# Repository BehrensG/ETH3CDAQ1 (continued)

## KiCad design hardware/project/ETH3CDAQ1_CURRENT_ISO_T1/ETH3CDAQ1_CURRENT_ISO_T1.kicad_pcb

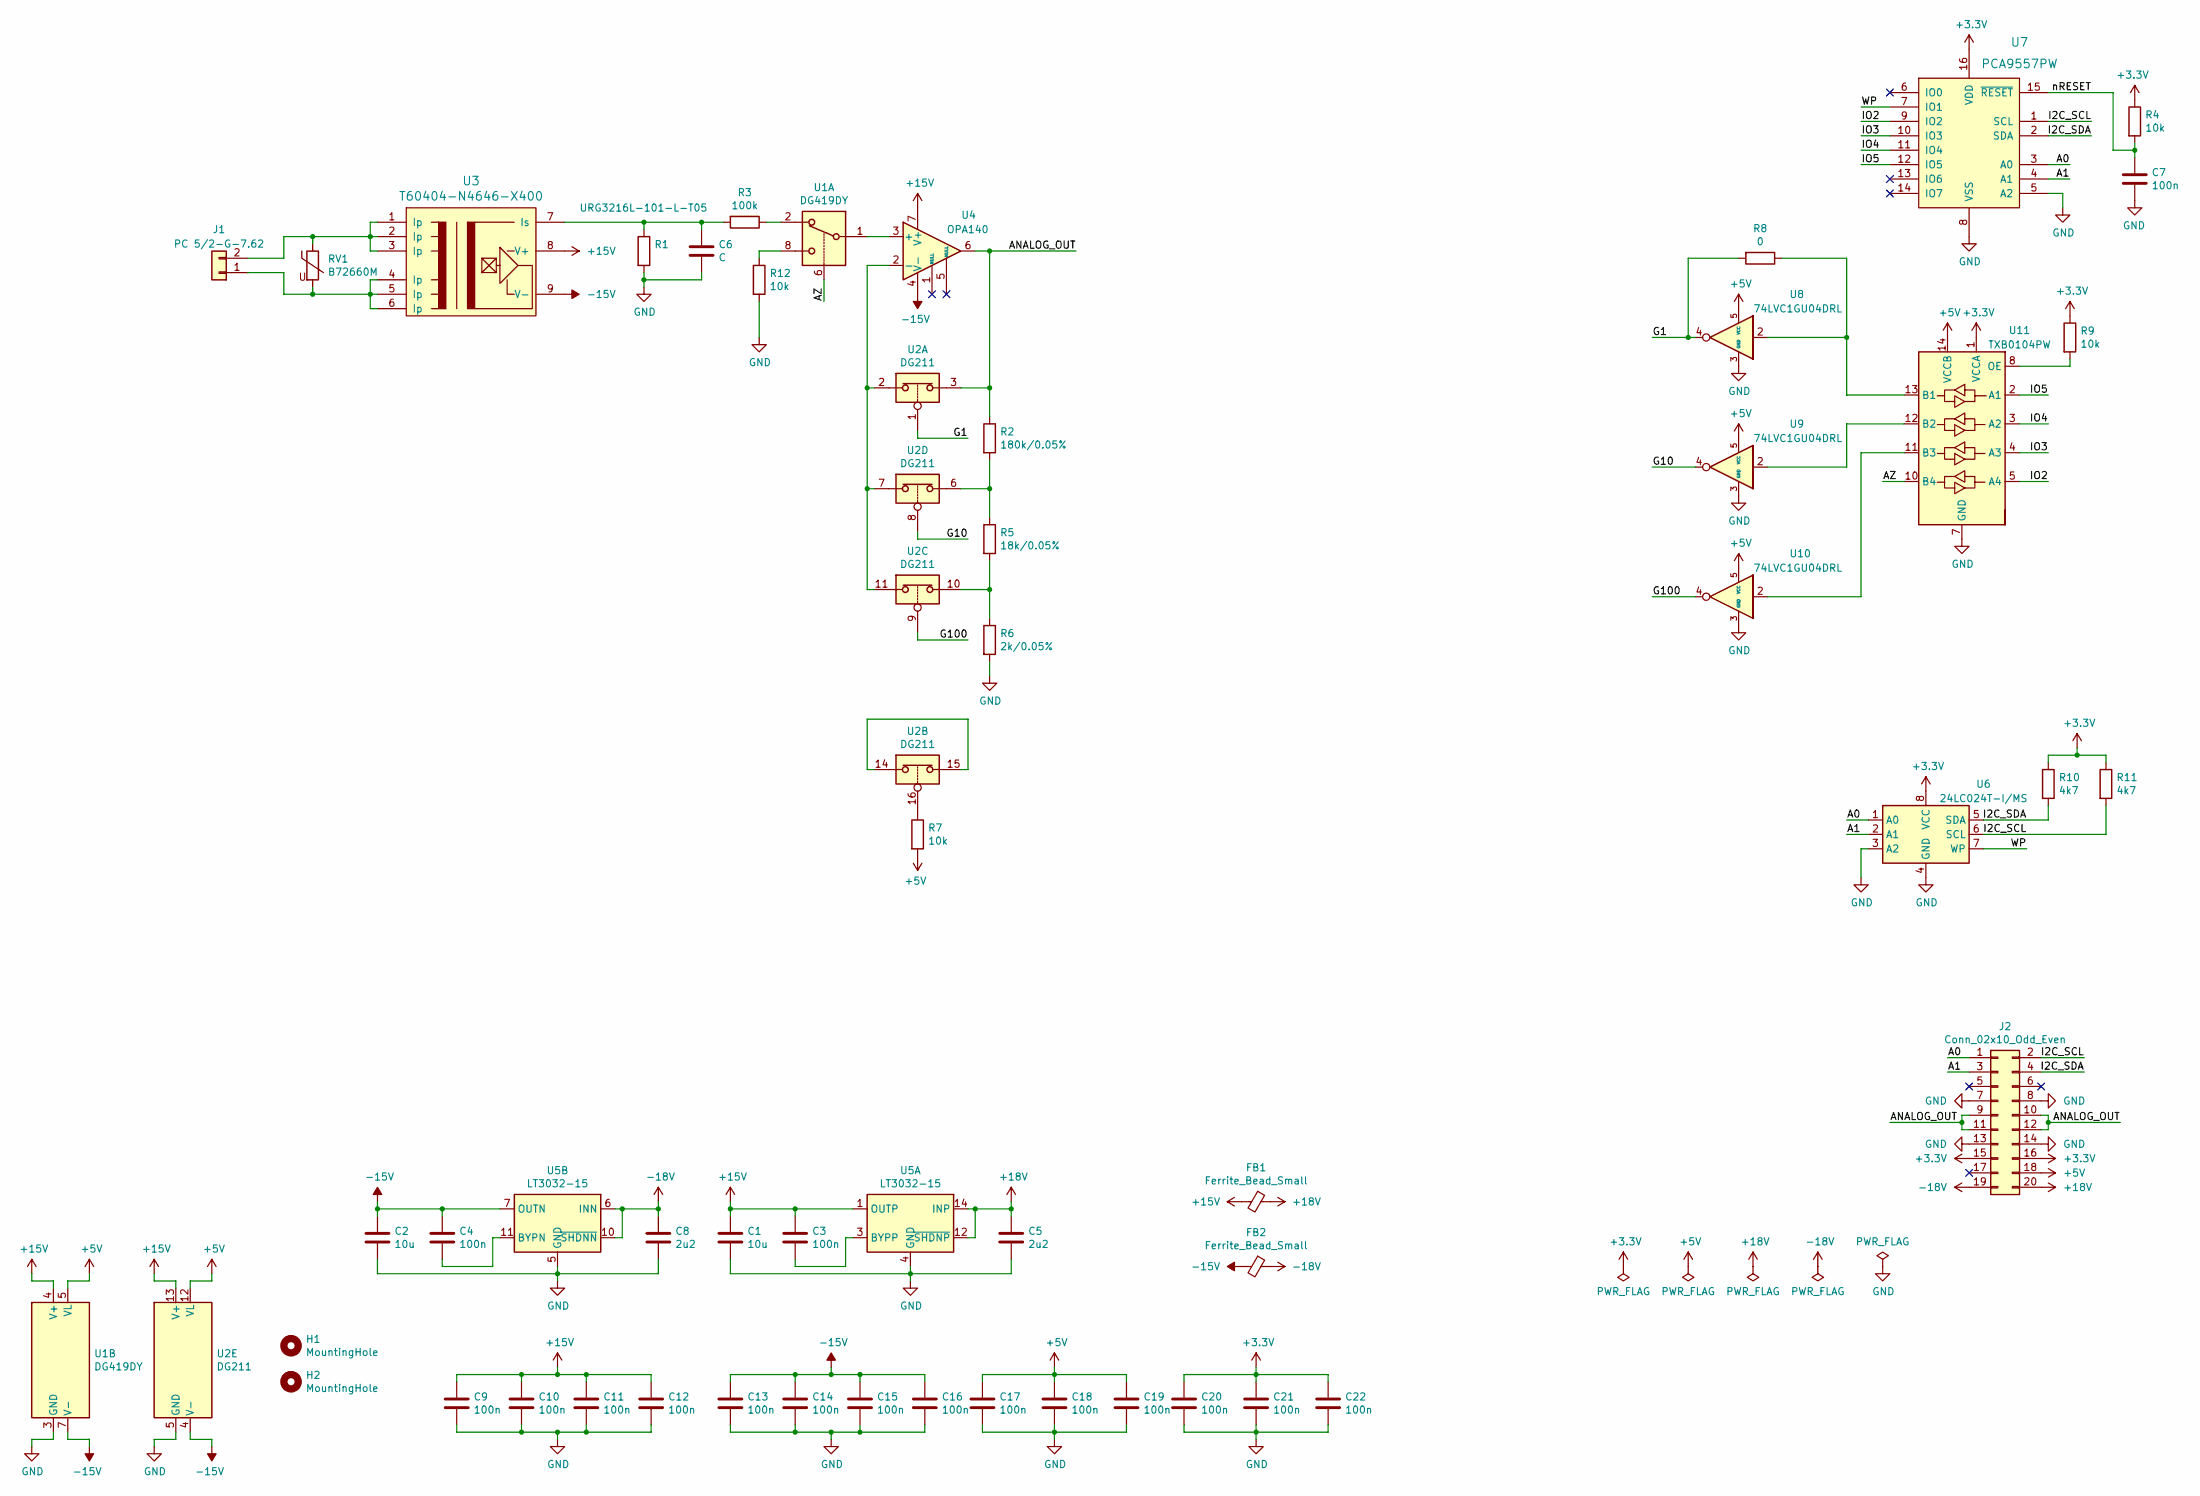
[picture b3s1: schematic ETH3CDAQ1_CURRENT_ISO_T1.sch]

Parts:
C1, C2: 10u; C_0603_1608Metric_Pad1.08x0.95mm_HandSolder
C3, C4, C7, C9, C10, C11, C12, C13, C14, C15, C16, C17, C18, C19, C20, C21, C22: 100n; C_0603_1608Metric_Pad1.08x0.95mm_HandSolder
C5, C8: 2u2; C_0603_1608Metric_Pad1.08x0.95mm_HandSolder
C6: C; C_1206_3216Metric_Pad1.33x1.80mm_HandSolder
FB1, FB2: Ferrite_Bead_Small; R_0603_1608Metric_Pad0.98x0.95mm_HandSolder
H1, H2: MountingHole; MountingHole_2.7mm_M2.5_DIN965_Pad
J1: PC 5/2-G-7.62; PC5_2-G-7_62
J2: Conn_02x10_Odd_Even; PinSocket_2x10_P2.54mm_Vertical
R1: URG3216L-101-L-T05; R_1206_3216Metric_Pad1.30x1.75mm_HandSolder
R2: 180k/0.05%; R_0603_1608Metric_Pad0.98x0.95mm_HandSolder
R3: 100k; R_0603_1608Metric_Pad0.98x0.95mm_HandSolder
R4, R7, R9, R12: 10k; R_0603_1608Metric_Pad0.98x0.95mm_HandSolder
R5: 18k/0.05%; R_0603_1608Metric_Pad0.98x0.95mm_HandSolder
R6: 2k/0.05%; R_0603_1608Metric_Pad0.98x0.95mm_HandSolder
R8: 0; R_0603_1608Metric_Pad0.98x0.95mm_HandSolder
R10, R11: 4k7; R_0603_1608Metric_Pad0.98x0.95mm_HandSolder
RV1: B72660M; 4032
U1: DG419DY; SOIC-8_3.9x4.9mm_P1.27mm
U2: DG211; TSSOP-16_4.4x5mm_P0.65mm
U3: T60404-N4646-X400
U4: OPA140; SOIC-8_3.9x4.9mm_P1.27mm
U5: LT3032-15; Linear_DE14MA
U6: 24LC024T-I/MS; MSOP-8_3x3mm_P0.65mm
U7: PCA9557PW; TSSOP-16_4.4x5mm_P0.65mm
U8, U9, U10: 74LVC1GU04DRL; SOT-553
U11: TXB0104PW; TSSOP-14_4.4x5mm_P0.65mm

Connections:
+3V3: C20.1, C21.1, C22.1, J2.15, J2.16, R4.1, R9.1, R10.1, R11.1, U6.8 (VCC), U7.16 (VDD), U11.1 (VCCA)
+5V: C17.1, C18.1, C19.1, J2.18, R7.2, U1.5 (VL), U2.12 (VL), U8.5 (VCC), U9.5 (VCC), U10.5 (VCC), U11.14 (VCCB)
+15V: C1.1, C3.1, C9.1, C10.1, C11.1, C12.1, FB1.2, U1.4 (V+), U2.13 (V+), U3.8 (V+), U4.7 (V+), U5.1 (OUTP)
+18V: C5.1, FB1.1, J2.20, U5.12 (~SHDNP), U5.14 (INP)
-15V: C2.1, C4.1, C13.1, C14.1, C15.1, C16.1, FB2.2, U1.7 (V-), U2.4 (V-), U3.9 (V-), U4.4 (V-), U5.7 (OUTN)
-18V: C8.1, FB2.1, J2.19, U5.6 (INN), U5.9 (INN), U5.10 (~SHDNN)
/A0: J2.1, U6.1 (A0), U7.3 (A0)
/A1: J2.3, U6.2 (A1), U7.4 (A1)
/ANALOG_OUT: J2.9, J2.10, J2.11, J2.12, R2.1, U2.3, U4.6
/AZ: U1.6, U11.10 (B4)
/G1: R8.2, U2.1, U8.4
/G10: U2.8, U9.4
/G100: U2.9, U10.4
/I2C_SCL: J2.2, R11.2, U6.6 (SCL), U7.1 (SCL)
/I2C_SDA: J2.4, R10.2, U6.5 (SDA), U7.2 (SDA)
/IO2: U7.9 (IO2), U11.5 (A4)
/IO3: U7.10 (IO3), U11.4 (A3)
/IO4: U7.11 (IO4), U11.3 (A2)
/IO5: U7.12 (IO5), U11.2 (A1)
/WP: U6.7 (WP), U7.7 (IO1)
/nRESET: C7.1, R4.2, U7.15 (~RESET)
GND: C1.2, C2.2, C5.2, C6.2, C7.2, C8.2, C9.2, C10.2, C11.2, C12.2, C13.2, C14.2, C15.2, C16.2, C17.2, C18.2, C19.2, C20.2, C21.2, C22.2, J2.7, J2.8, J2.13, J2.14, R1.2, R6.2, R12.2, U1.3 (GND), U2.5 (GND), U5.4 (GND), U5.5 (GND), U6.3 (A2), U6.4 (GND), U7.5 (A2), U7.8 (VSS), U8.3 (GND), U9.3 (GND), U10.3 (GND), U11.7 (GND)
unnamed: C3.2, U5.3 (BYPP)
unnamed: C4.2, U5.11 (BYPN)
unnamed: C6.1, R1.1, R3.2, U3.7 (Is)
unnamed: J1.1, RV1.2, U3.4 (Ip), U3.5 (Ip), U3.6 (Ip)
unnamed: J1.2, RV1.1, U3.1 (Ip), U3.2 (Ip), U3.3 (Ip)
unnamed: R2.2, R5.1, U2.6
unnamed: R3.1, U1.2
unnamed: R5.2, R6.1, U2.10
unnamed: R7.1, U2.16
unnamed: R8.1, U8.2, U11.13 (B1)
unnamed: R9.2, U11.8 (OE)
unnamed: R12.1, U1.8
unnamed: U1.1, U4.3 (+)
unnamed: U2.2, U2.7, U2.11, U4.2 (-)
unnamed: U2.14, U2.15
unnamed: U10.2, U11.11 (B3)
unnamed: U9.2, U11.12 (B2)

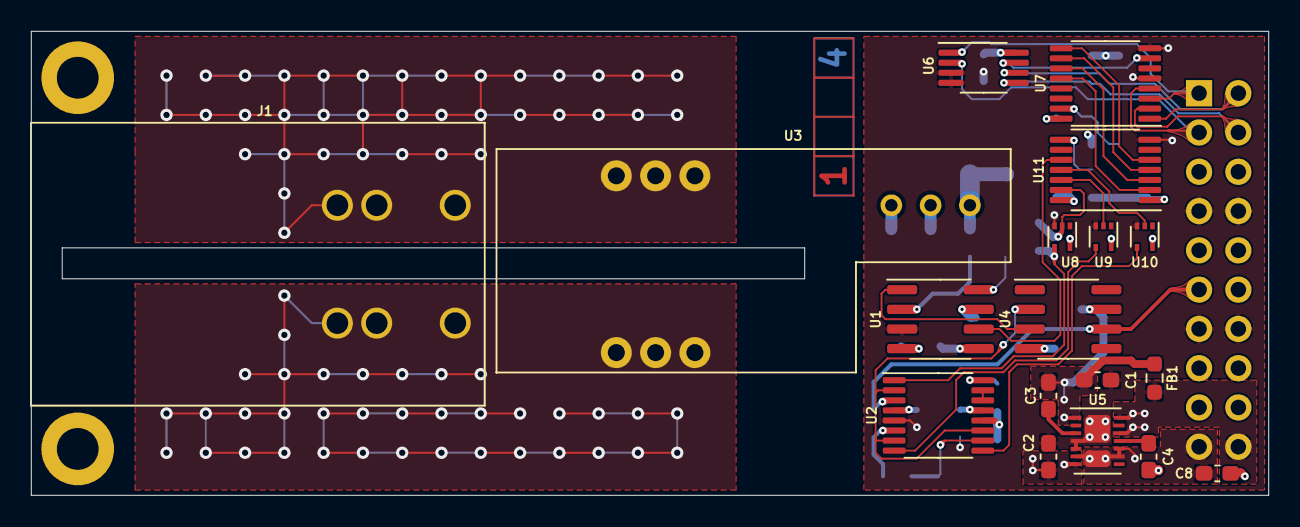
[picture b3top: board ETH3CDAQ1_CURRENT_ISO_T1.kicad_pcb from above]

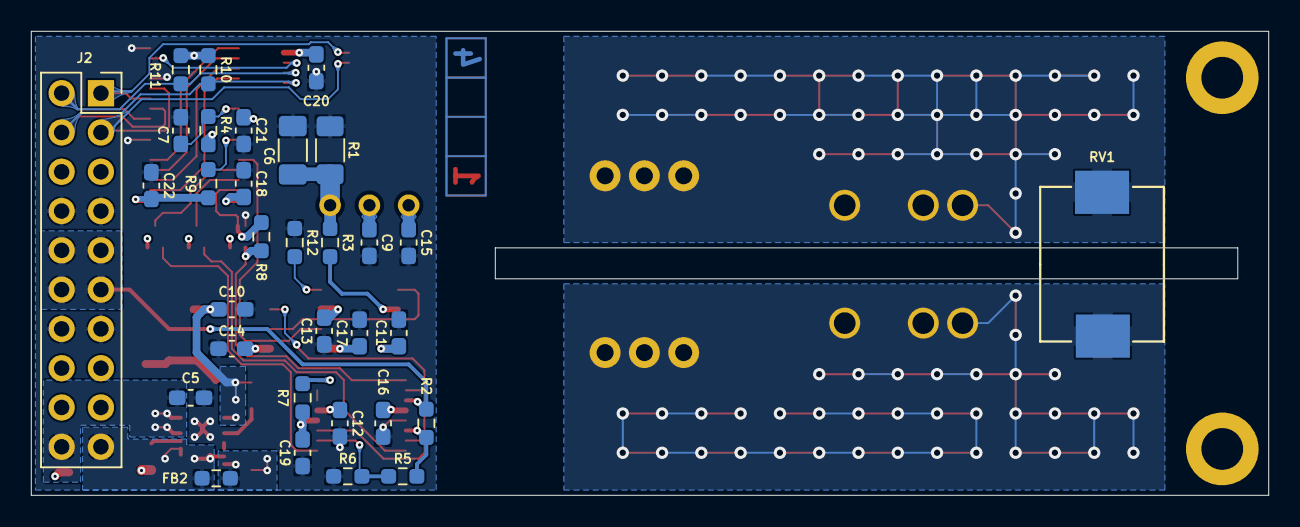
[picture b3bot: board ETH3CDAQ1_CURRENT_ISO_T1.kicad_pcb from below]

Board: 4 copper layers, 80.0 x 30.0 mm, 52 parts (32 on the bottom side), 39 nets.

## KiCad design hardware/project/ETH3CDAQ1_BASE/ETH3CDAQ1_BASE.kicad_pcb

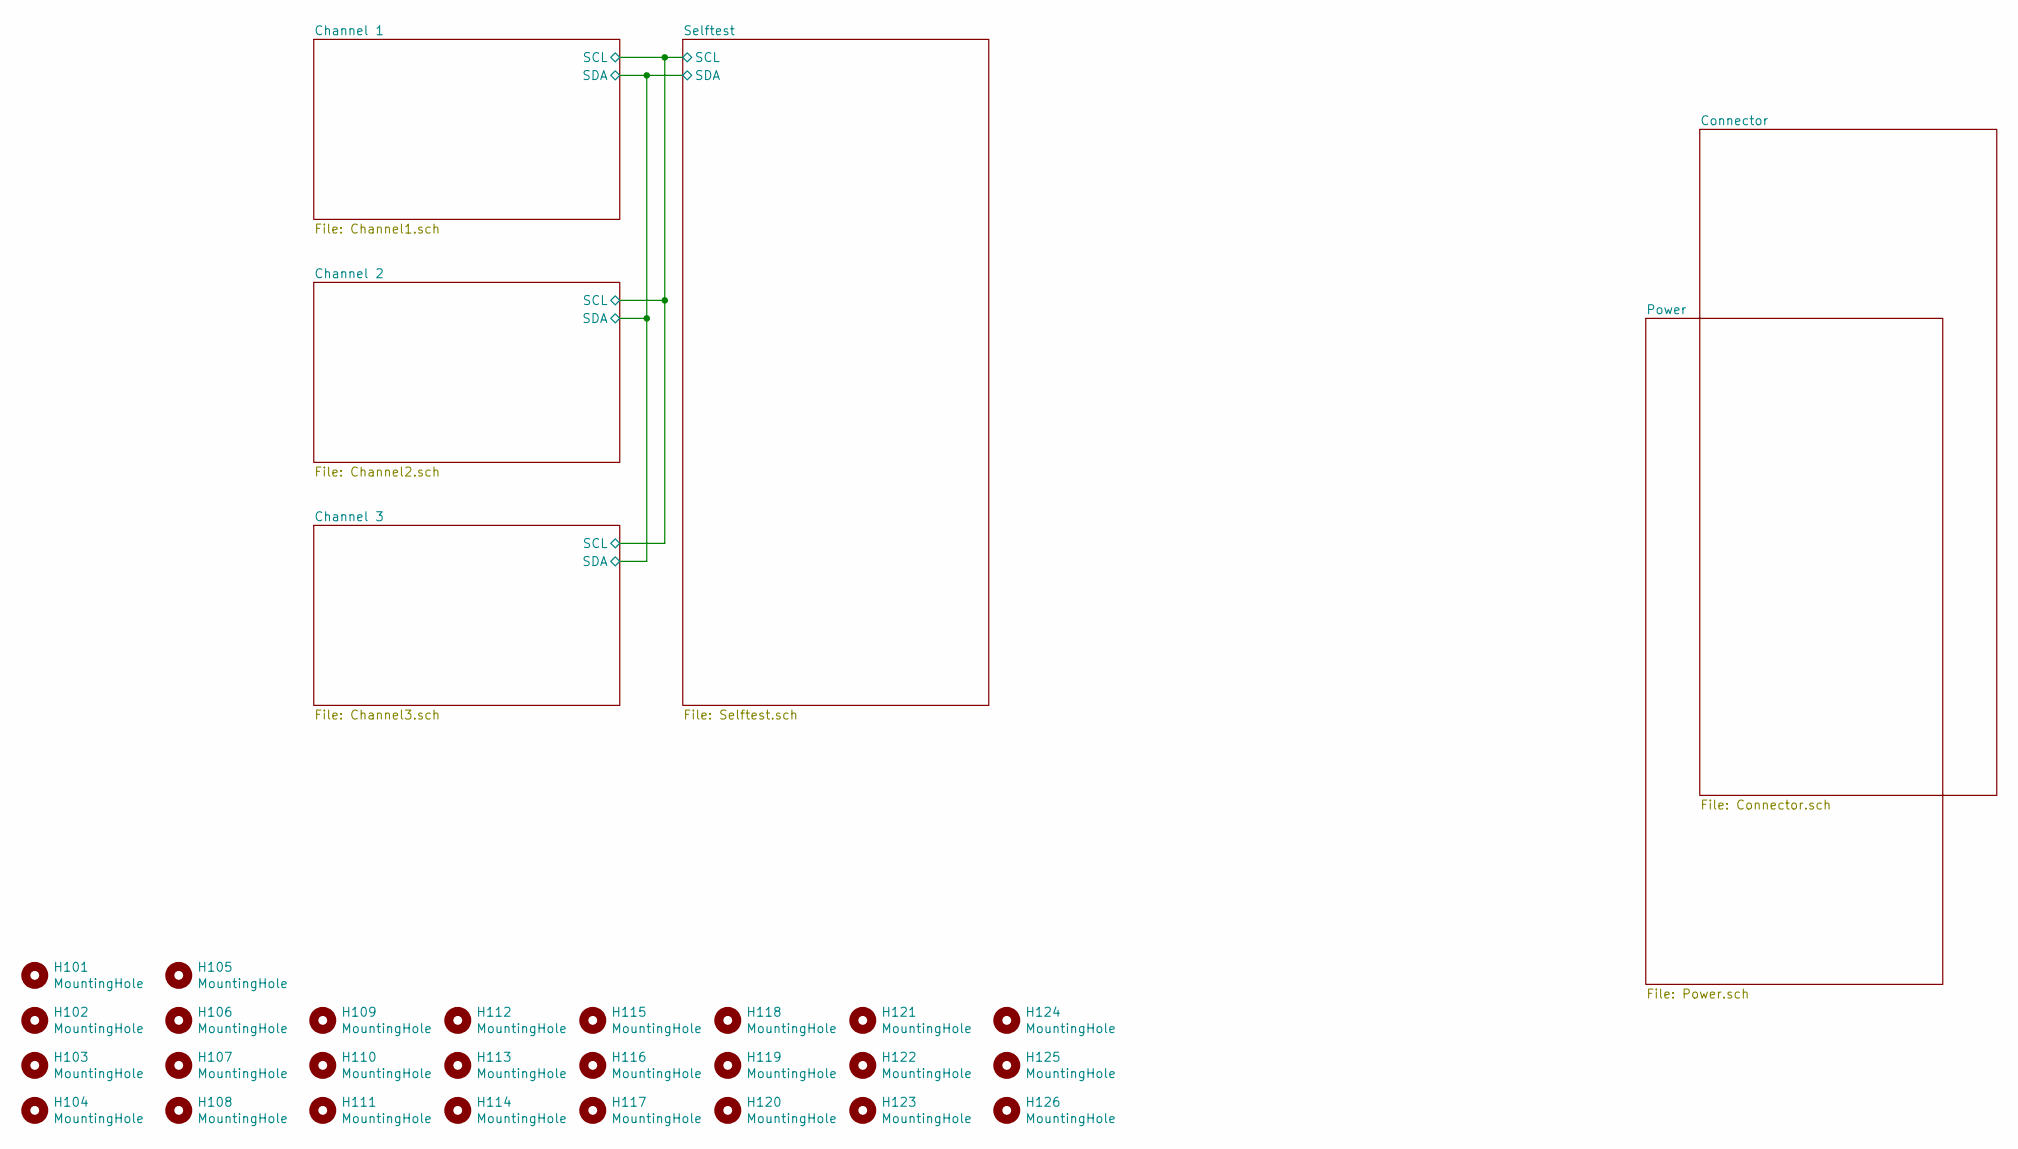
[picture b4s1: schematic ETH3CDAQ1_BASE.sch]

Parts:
H101, H105: MountingHole; MountingHole_3.2mm_M3_DIN965_Pad
H102, H103, H104, H106, H107, H108, H109, H110, H111, H112, H113, H114, H115, H116, H117, H118, H119, H120, H121, H122, H123, H124, H125, H126: MountingHole; MountingHole_2.7mm_M2.5_DIN965_Pad

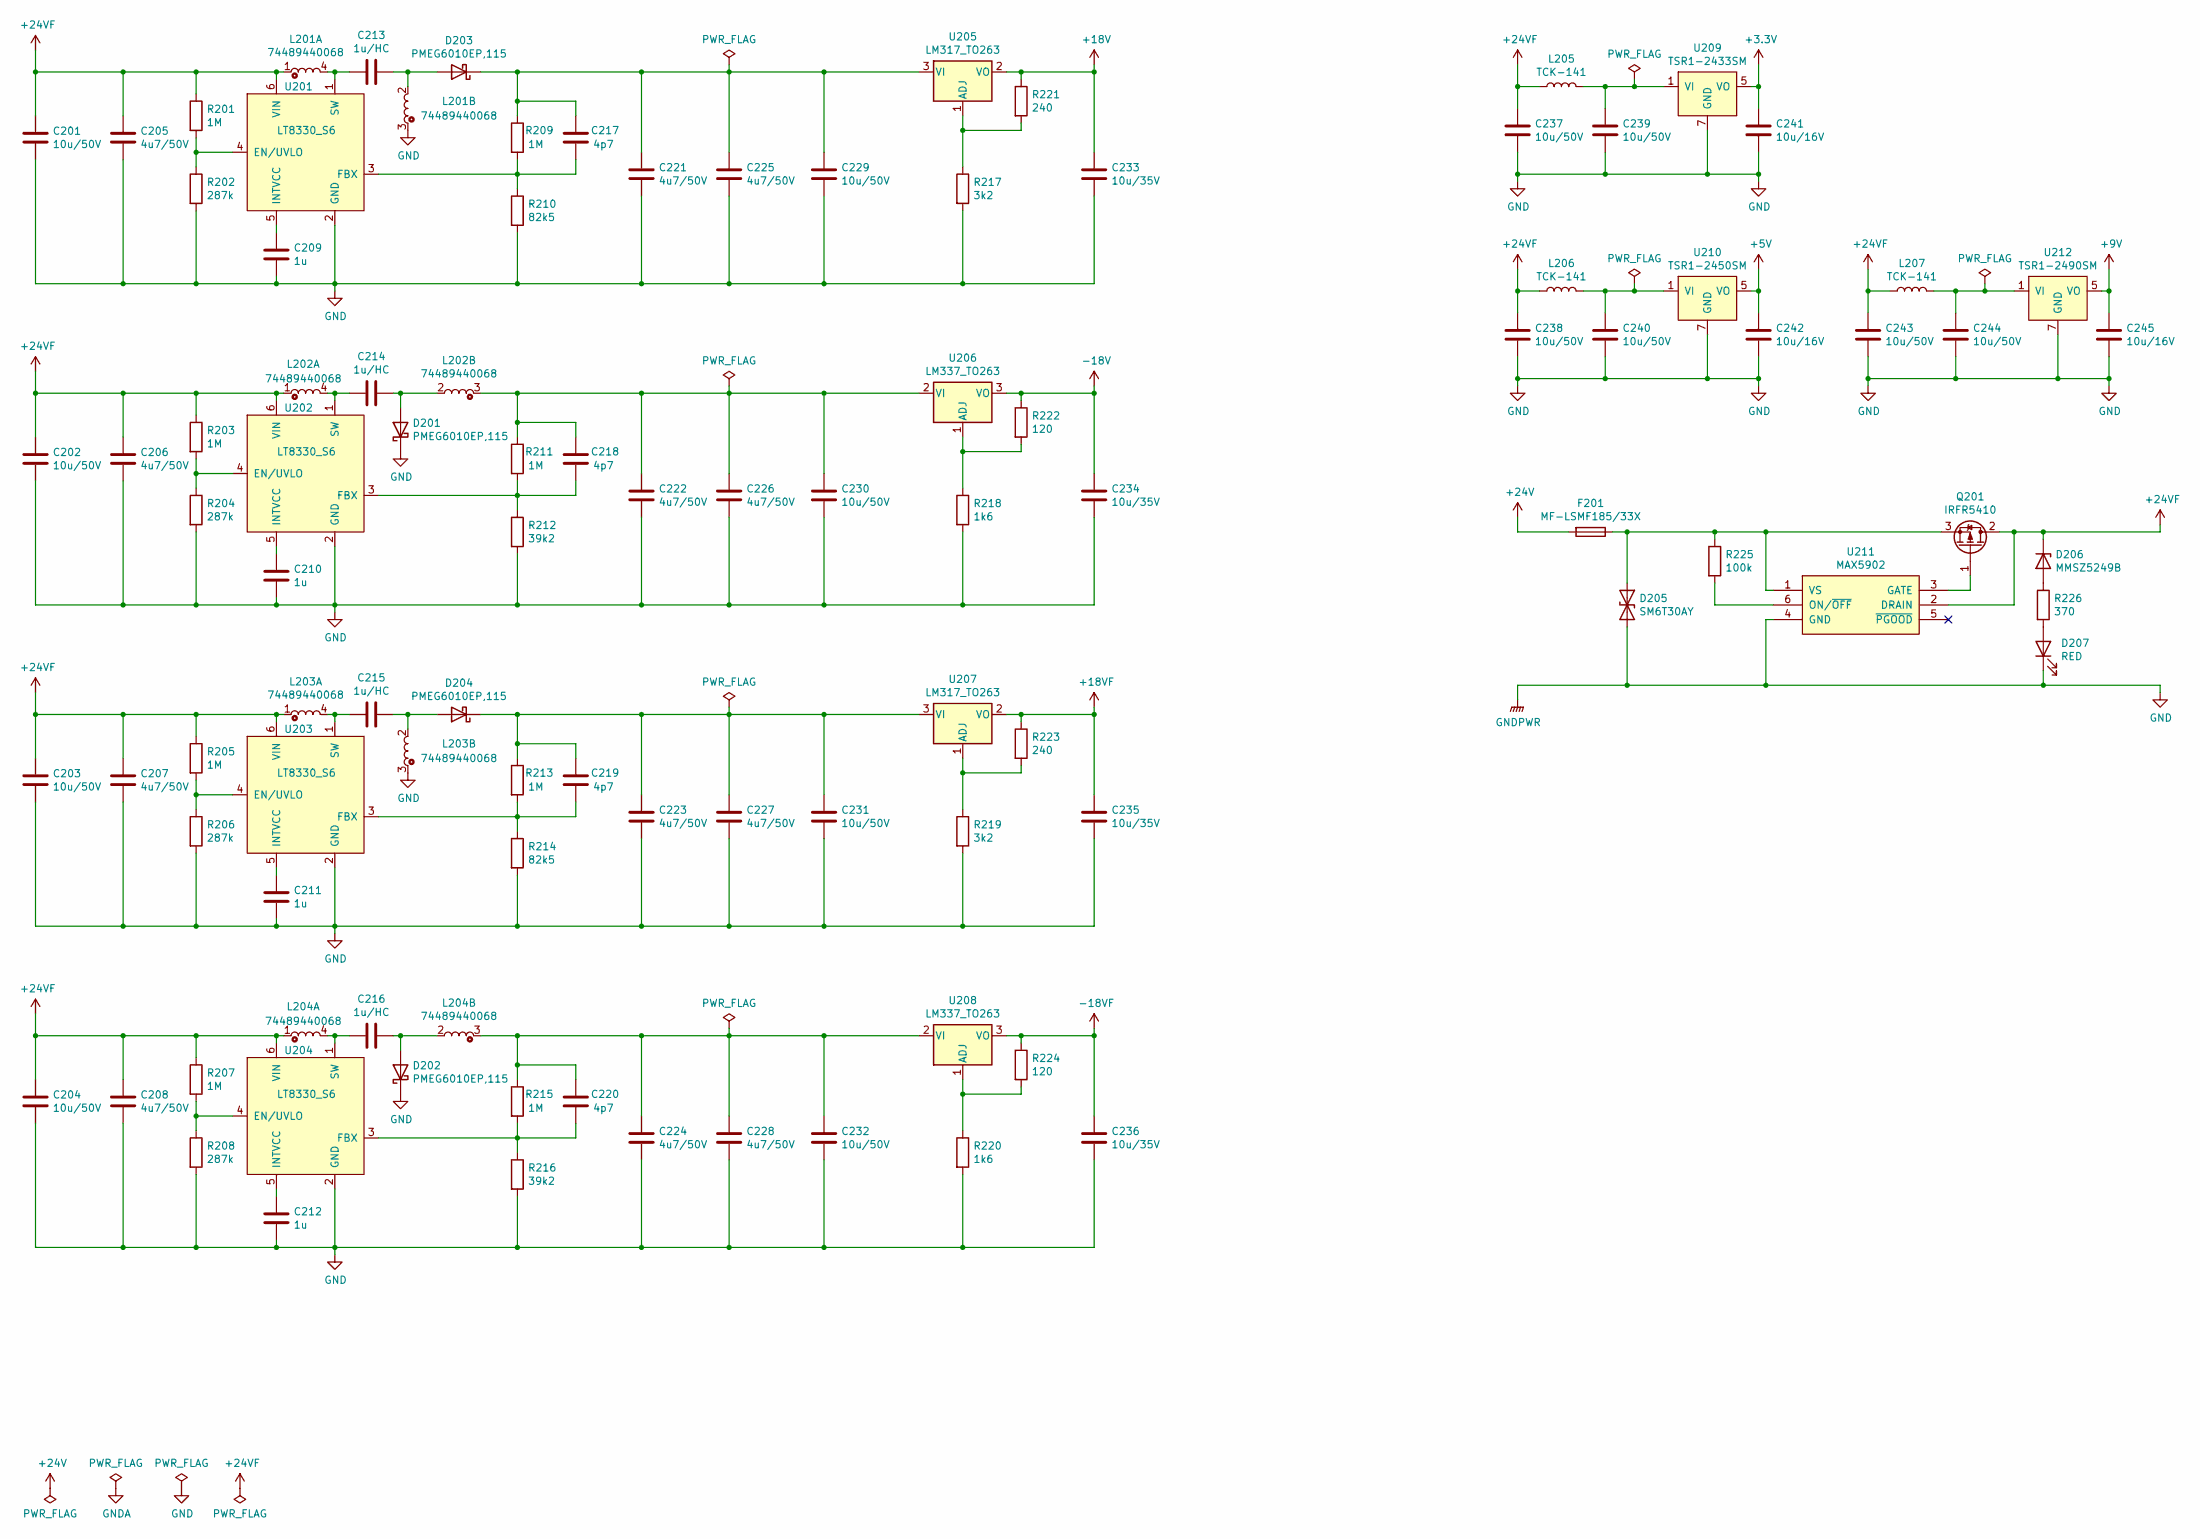
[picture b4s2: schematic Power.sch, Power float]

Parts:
C201, C202, C203, C204, C229, C230, C231, C232, C237, C238, C239, C240, C243, C244: 10u/50V; C_1206_3216Metric_Pad1.33x1.80mm_HandSolder
C205, C206, C207, C208, C221, C222, C223, C224, C225, C226, C227, C228: 4u7/50V; C_1206_3216Metric_Pad1.33x1.80mm_HandSolder
C209, C210, C211, C212: 1u; C_0603_1608Metric_Pad1.08x0.95mm_HandSolder
C213, C214, C215, C216: 1u/HC; C_1206_3216Metric_Pad1.33x1.80mm_HandSolder
C217, C218, C219, C220: 4p7; C_0603_1608Metric_Pad1.08x0.95mm_HandSolder
C233, C234, C235, C236: 10u/35V; C_1206_3216Metric_Pad1.33x1.80mm_HandSolder
C241, C242, C245: 10u/16V; C_1206_3216Metric_Pad1.33x1.80mm_HandSolder
D201, D202, D203, D204: PMEG6010EP,115; D_SOD-128
D205: SM6T30AY; DO_214AA_REV
D206: MMSZ5249B; D_SOD-123
D207: RED; LED_0603_1608Metric_Pad1.05x0.95mm_HandSolder
F201: MF-LSMF185/33X; Fuse_SMD2920
L201, L202, L203, L204: 74489440068
L205, L206, L207: TCK-141
Q201: IRFR5410; TO-252-2_Rectifier
R201, R203, R205, R207, R209, R211, R213, R215: 1M; R_0603_1608Metric_Pad0.98x0.95mm_HandSolder
R202, R204, R206, R208: 287k; R_0603_1608Metric_Pad0.98x0.95mm_HandSolder
R210, R214: 82k5; R_0603_1608Metric_Pad0.98x0.95mm_HandSolder
R212, R216: 39k2; R_0603_1608Metric_Pad0.98x0.95mm_HandSolder
R217, R219: 3k2; R_0603_1608Metric_Pad1.05x0.95mm_HandSolder
R218, R220: 1k6; R_0603_1608Metric_Pad1.05x0.95mm_HandSolder
R221, R223: 240; R_0603_1608Metric_Pad1.05x0.95mm_HandSolder
R222, R224: 120; R_0603_1608Metric_Pad1.05x0.95mm_HandSolder
R225: 100k; R_0603_1608Metric_Pad0.98x0.95mm_HandSolder
R226: 370; R_0603_1608Metric_Pad0.98x0.95mm_HandSolder
U201, U202, U203, U204: LT8330_S6; TSOT-23-6_HandSoldering
U205, U207: LM317_TO263; TO-263-3_TabPin2
U206, U208: LM337_TO263; TO-263-2
U209: TSR1-2433SM; TSR1SM
U210: TSR1-2450SM; TSR1SM
U211: MAX5902; SOT-23-6_Handsoldering
U212: TSR1-2490SM; TSR1SM

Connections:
+3V3: C241.1, U209.5 (VO); also elsewhere on the board
+5V: C242.1, U210.5 (VO); also elsewhere on the board
+9V: C245.1, U212.5 (VO); also elsewhere on the board
+18V: C233.1, R221.1, U205.2 (VO); also elsewhere on the board
+18VF: C235.1, R223.1, U207.2 (VO); also elsewhere on the board
+24V: F201.2; also elsewhere on the board
+24VF: C201.1, C202.1, C203.1, C204.1, C205.1, C206.1, C207.1, C208.1, C237.1, C238.1, C243.1, D206.1 (K), L201.1, L202.1, L203.1, L204.1, L205.1, L206.1, L207.1, Q201.2 (D), R201.1, R203.1, R205.1, R207.1, U201.6 (VIN), U202.6 (VIN), U203.6 (VIN), U204.6 (VIN), U211.2 (DRAIN)
-18V: C234.1, R222.1, U206.3 (VO); also elsewhere on the board
-18VF: C236.1, R224.1, U208.3 (VO); also elsewhere on the board
unnamed: C209.1, U201.5 (INTVCC)
unnamed: C210.1, U202.5 (INTVCC)
unnamed: C211.1, U203.5 (INTVCC)
unnamed: C212.1, U204.5 (INTVCC)
unnamed: C213.1, D203.2 (A), L201.2
unnamed: C213.2, L201.4, U201.1 (SW)
unnamed: C214.1, D201.2 (A), L202.2
unnamed: C214.2, L202.4, U202.1 (SW)
unnamed: C215.1, D204.2 (A), L203.2
unnamed: C215.2, L203.4, U203.1 (SW)
unnamed: C216.1, D202.2 (A), L204.2
unnamed: C216.2, L204.4, U204.1 (SW)
unnamed: C217.1, C221.1, C225.1, C229.1, D203.1 (K), R209.1, U205.3 (VI)
unnamed: C217.2, R209.2, R210.1, U201.3 (FBX)
unnamed: C218.1, C222.1, C226.1, C230.1, L202.3, R211.1, U206.2 (VI)
unnamed: C218.2, R211.2, R212.1, U202.3 (FBX)
unnamed: C219.1, C223.1, C227.1, C231.1, D204.1 (K), R213.1, U207.3 (VI)
unnamed: C219.2, R213.2, R214.1, U203.3 (FBX)
unnamed: C220.1, C224.1, C228.1, C232.1, L204.3, R215.1, U208.2 (VI)
unnamed: C220.2, R215.2, R216.1, U204.3 (FBX)
unnamed: C239.1, L205.2, U209.1 (VI)
unnamed: C240.1, L206.2, U210.1 (VI)
unnamed: C244.1, L207.2, U212.1 (VI)
unnamed: D205.1 (A1), F201.1, Q201.3 (S), R225.1, U211.1 (VS)
unnamed: D206.2 (A), R226.1
unnamed: D207.2 (A), R226.2
unnamed: Q201.1 (G), U211.3 (GATE)
unnamed: R201.2, R202.1, U201.4 (EN/UVLO)
unnamed: R203.2, R204.1, U202.4 (EN/UVLO)
unnamed: R205.2, R206.1, U203.4 (EN/UVLO)
unnamed: R207.2, R208.1, U204.4 (EN/UVLO)
unnamed: R217.1, R221.2, U205.1 (ADJ)
unnamed: R218.1, R222.2, U206.1 (ADJ)
unnamed: R219.1, R223.2, U207.1 (ADJ)
unnamed: R220.1, R224.2, U208.1 (ADJ)
unnamed: R225.2, U211.6 (ON/~OFF)

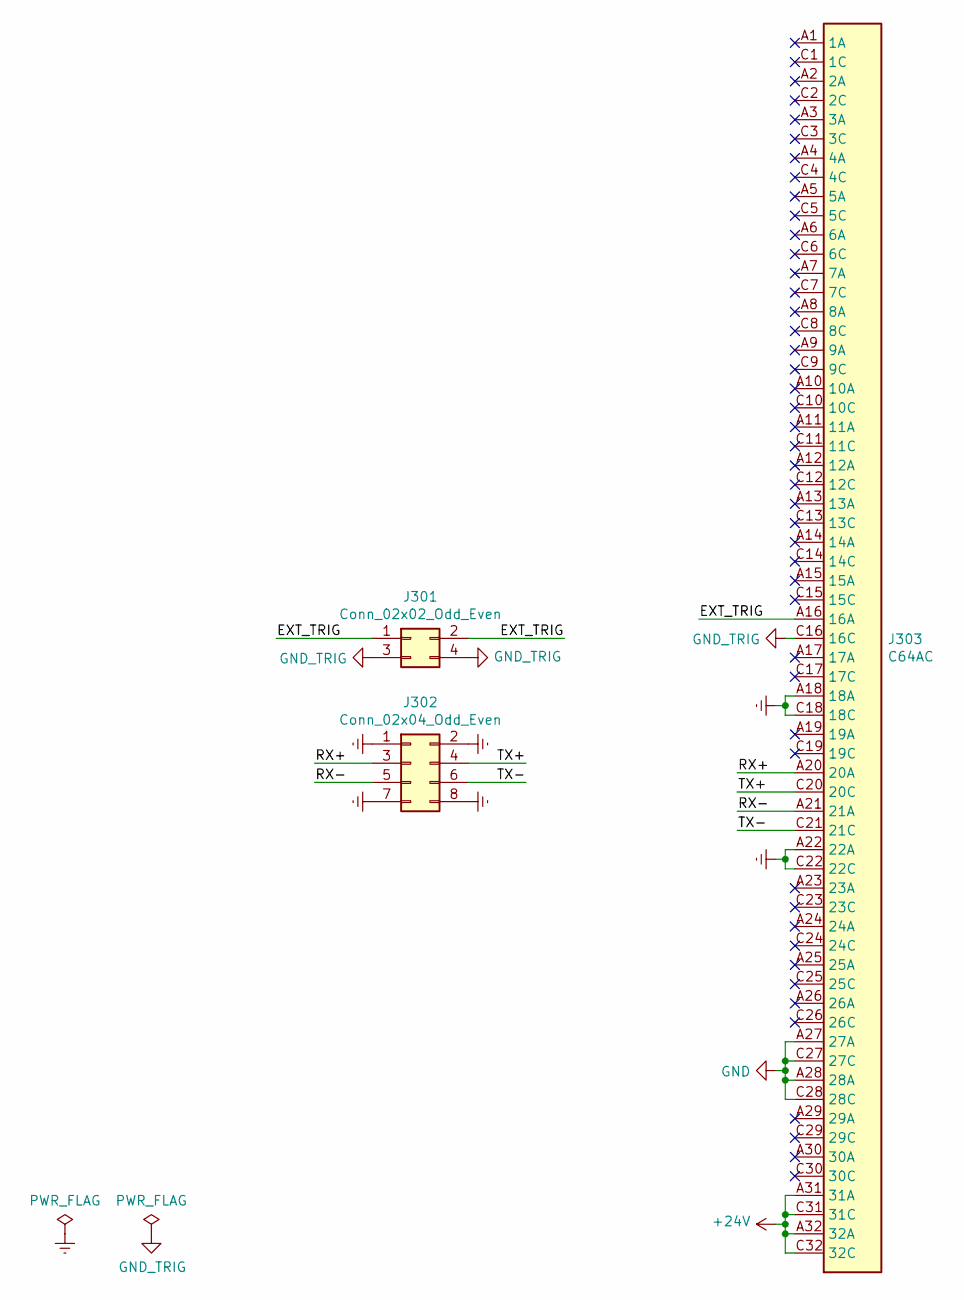
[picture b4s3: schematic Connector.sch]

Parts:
J301: Conn_02x02_Odd_Even; PinHeader_2x02_P2.54mm_Vertical
J302: Conn_02x04_Odd_Even; PinHeader_2x04_P2.54mm_Vertical
J303: C64AC; Socket_DIN41612-CaseC1-AC-Male-64Pin-2rows

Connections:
+24V: J303.A31 (31A), J303.A32 (32A), J303.C31 (31C), J303.C32 (32C); also elsewhere on the board
/Connector/EXT_TRIG: J301.1, J301.2, J303.A16 (16A)
/Connector/RX+: J302.3, J303.A20 (20A)
/Connector/RX-: J302.5, J303.A21 (21A)
/Connector/TX+: J302.4, J303.C20 (20C)
/Connector/TX-: J302.6, J303.C21 (21C)
Earth: J302.1, J302.2, J302.7, J302.8, J303.A18 (18A), J303.A22 (22A), J303.C18 (18C), J303.C22 (22C)
GND_TRIG: J301.3, J301.4, J303.C16 (16C)

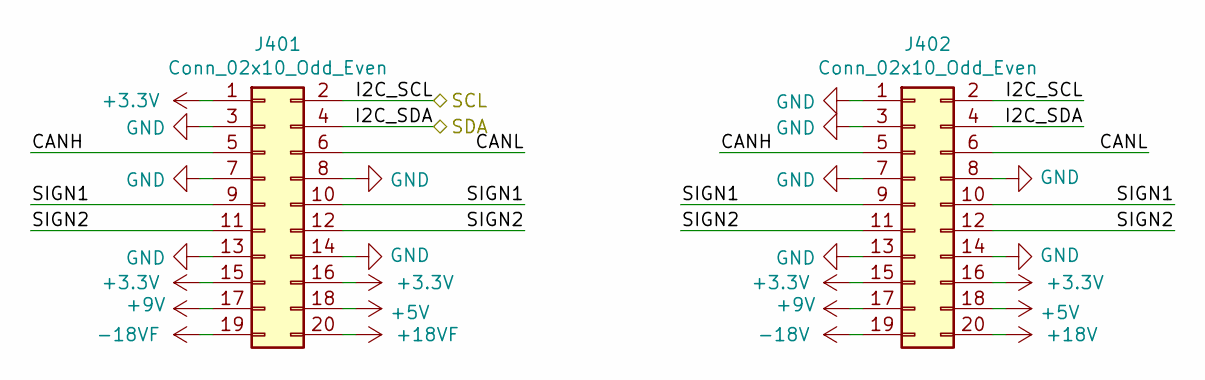
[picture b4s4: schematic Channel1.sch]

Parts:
J401, J402: Conn_02x10_Odd_Even; PinHeader_2x10_P2.54mm_Vertical

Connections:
+3V3: J401.1, J401.15, J401.16, J402.15, J402.16; also elsewhere on the board
+5V: J401.18, J402.18; also elsewhere on the board
+9V: J401.17, J402.17; also elsewhere on the board
+18V: J402.20; also elsewhere on the board
+18VF: J401.20; also elsewhere on the board
-18V: J402.19; also elsewhere on the board
-18VF: J401.19; also elsewhere on the board
/Channel 1/CANH: J401.5, J402.5
/Channel 1/CANL: J401.6, J402.6
/Channel 1/SCL: J401.2, J402.2; also elsewhere on the board
/Channel 1/SDA: J401.4, J402.4; also elsewhere on the board
/Channel 1/SIGN1: J401.9, J401.10, J402.9, J402.10
/Channel 1/SIGN2: J401.11, J401.12, J402.11, J402.12

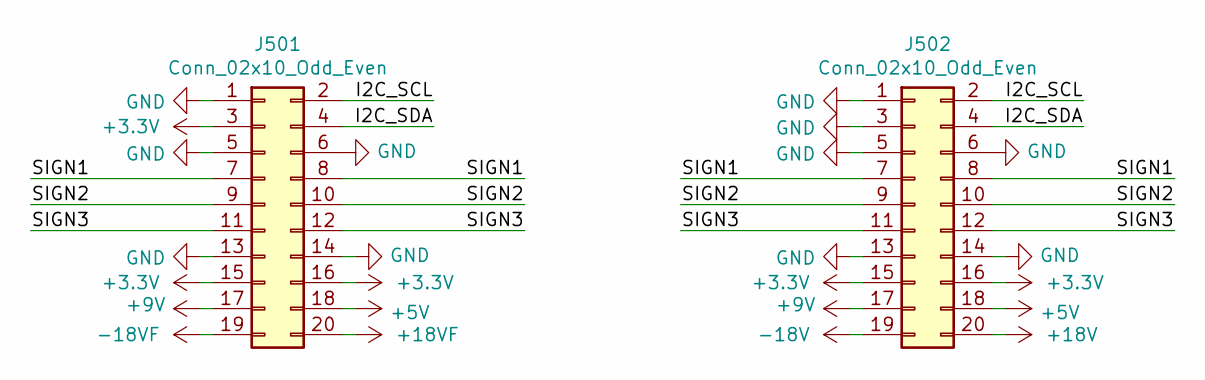
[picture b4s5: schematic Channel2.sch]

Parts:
J501, J502: Conn_02x10_Odd_Even; PinHeader_2x10_P2.54mm_Vertical

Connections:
+3V3: J501.3, J501.15, J501.16, J502.15, J502.16; also elsewhere on the board
+5V: J501.18, J502.18; also elsewhere on the board
+9V: J501.17, J502.17; also elsewhere on the board
+18V: J502.20; also elsewhere on the board
+18VF: J501.20; also elsewhere on the board
-18V: J502.19; also elsewhere on the board
-18VF: J501.19; also elsewhere on the board
/Channel 1/SCL: J501.2, J502.2; also elsewhere on the board
/Channel 1/SDA: J501.4, J502.4; also elsewhere on the board
/Channel 2/SIGN1: J501.9, J501.10, J502.9, J502.10
/Channel 2/SIGN2: J501.11, J501.12, J502.11, J502.12

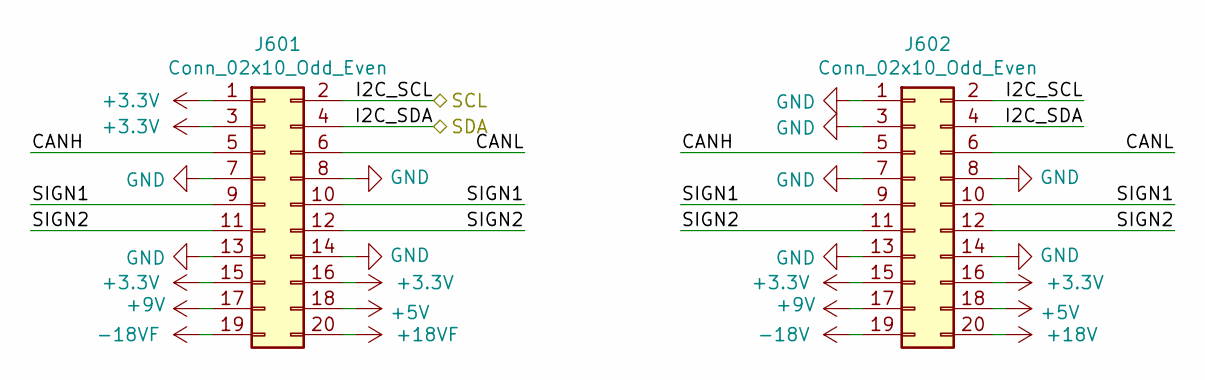
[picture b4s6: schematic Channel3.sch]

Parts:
J601, J602: Conn_02x10_Odd_Even; PinHeader_2x10_P2.54mm_Vertical

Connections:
+3V3: J601.1, J601.3, J601.15, J601.16, J602.15, J602.16; also elsewhere on the board
+5V: J601.18, J602.18; also elsewhere on the board
+9V: J601.17, J602.17; also elsewhere on the board
+18V: J602.20; also elsewhere on the board
+18VF: J601.20; also elsewhere on the board
-18V: J602.19; also elsewhere on the board
-18VF: J601.19; also elsewhere on the board
/Channel 1/SCL: J601.2, J602.2; also elsewhere on the board
/Channel 1/SDA: J601.4, J602.4; also elsewhere on the board
/Channel 3/CANH: J601.5, J602.5
/Channel 3/CANL: J601.6, J602.6
/Channel 3/SIGN1: J601.9, J601.10, J602.9, J602.10
/Channel 3/SIGN2: J601.11, J601.12, J602.11, J602.12

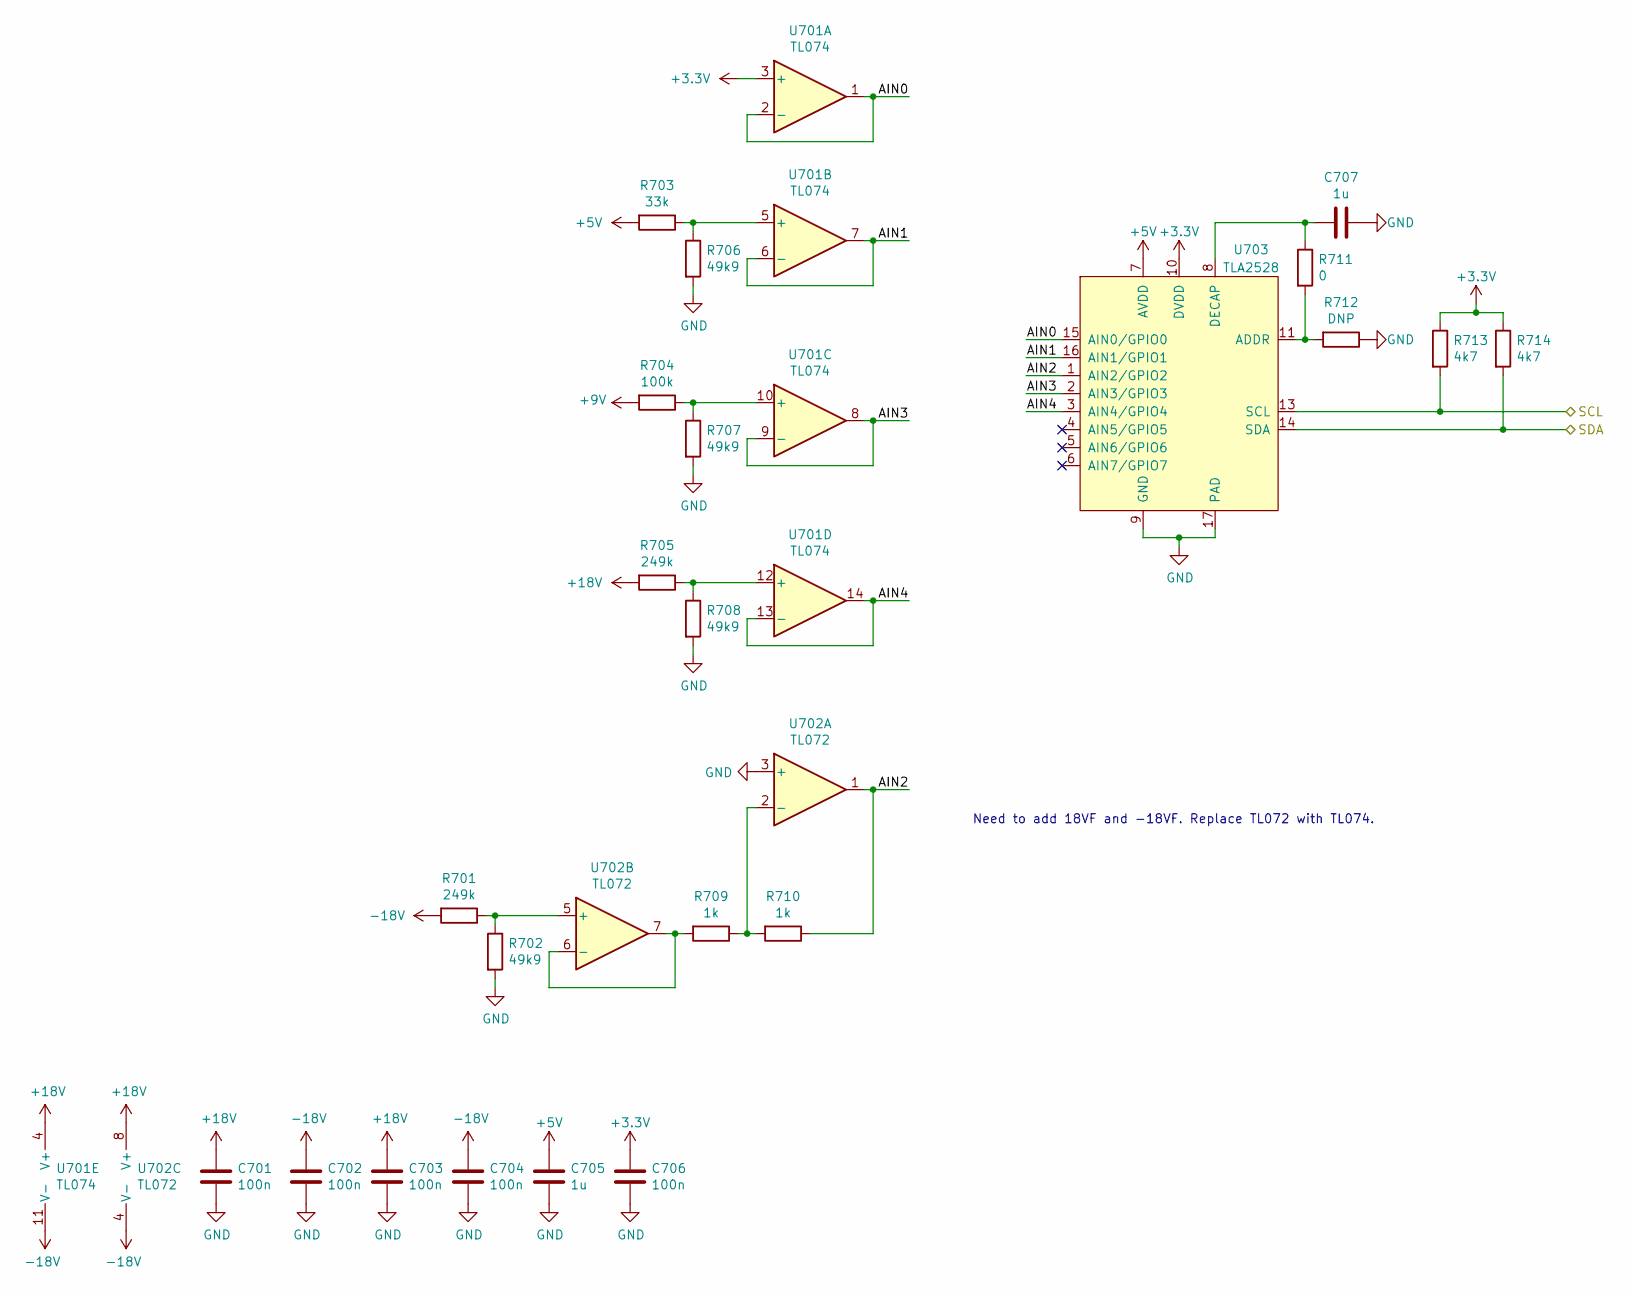
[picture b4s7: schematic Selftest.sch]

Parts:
C701, C702, C703, C704, C706: 100n; C_0603_1608Metric_Pad1.08x0.95mm_HandSolder
C705, C707: 1u; C_0603_1608Metric_Pad1.08x0.95mm_HandSolder
R701, R705: 249k; R_0603_1608Metric_Pad0.98x0.95mm_HandSolder
R702, R706, R707, R708: 49k9; R_0603_1608Metric_Pad0.98x0.95mm_HandSolder
R703: 33k; R_0603_1608Metric_Pad0.98x0.95mm_HandSolder
R704: 100k; R_0603_1608Metric_Pad0.98x0.95mm_HandSolder
R709, R710: 1k; R_0603_1608Metric_Pad0.98x0.95mm_HandSolder
R711: 0; R_0603_1608Metric_Pad0.98x0.95mm_HandSolder
R712: DNP; R_0603_1608Metric_Pad0.98x0.95mm_HandSolder
R713, R714: 4k7; R_0603_1608Metric_Pad0.98x0.95mm_HandSolder
U701: TL074; TSSOP-14_4.4x5mm_P0.65mm
U702: TL072; SO-8_3.9x4.9mm_P1.27mm
U703: TLA2528; WQFN-16-1EP_3x3mm_P0.5mm_EP1.6x1.6mm_ThermalVias

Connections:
+3V3: C706.2, R713.1, R714.1, U701.3 (+), U703.10 (DVDD); also elsewhere on the board
+5V: C705.2, R703.2, U703.7 (AVDD); also elsewhere on the board
+9V: R704.2; also elsewhere on the board
+18V: C701.2, C703.2, R705.2, U701.4 (V+), U702.8 (V+); also elsewhere on the board
-18V: C702.2, C704.2, R701.2, U701.11 (V-), U702.4 (V-); also elsewhere on the board
/Channel 1/SCL: R713.2, U703.13 (SCL); also elsewhere on the board
/Channel 1/SDA: R714.2, U703.14 (SDA); also elsewhere on the board
/Selftest/AIN0: U701.1, U701.2 (-), U703.15 (AIN0/GPIO0)
/Selftest/AIN1: U701.6 (-), U701.7, U703.16 (AIN1/GPIO1)
/Selftest/AIN2: R710.1, U702.1, U703.1 (AIN2/GPIO2)
/Selftest/AIN3: U701.8, U701.9 (-), U703.2 (AIN3/GPIO3)
/Selftest/AIN4: U701.13 (-), U701.14, U703.3 (AIN4/GPIO4)
unnamed: C707.2, R711.1, U703.8 (DECAP)
unnamed: R701.1, R702.1, U702.5 (+)
unnamed: R703.1, R706.1, U701.5 (+)
unnamed: R704.1, R707.1, U701.10 (+)
unnamed: R705.1, R708.1, U701.12 (+)
unnamed: R709.1, R710.2, U702.2 (-)
unnamed: R709.2, U702.6 (-), U702.7
unnamed: R711.2, R712.2, U703.11 (ADDR)

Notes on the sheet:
Need to add 18VF and -18VF. Replace TL072 with TL074.

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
